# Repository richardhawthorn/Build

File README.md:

### Description

'Build' is an interchangeable set of input/output boards that let you create a complex system of sensors, buttons, actuators, transmitters and screens. Build starts with a wifi base and adds 13 different individually addressed i/o boards.  All boards clip together using a standard 6 pin header, so expanding the system quick and easy. 

This work is licensed under a Creative Commons Attribution-ShareAlike 4.0 International License.

<br />
Designed by <a xmlns:cc="http://creativecommons.org/ns#" href="http://www.richardhawthorn.com" property="cc:attributionName" rel="cc:attributionURL" target="_blank">Richard Hawthorn</a><br />
<a rel="license" href="http://creativecommons.org/licenses/by-sa/4.0/" target="_blank">View License</a>

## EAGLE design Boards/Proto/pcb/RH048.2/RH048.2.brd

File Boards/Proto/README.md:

### Description

Prototype board for use in build system

### Features

- Prototype space
- 3.3v operation

### License

This work is licensed under a Creative Commons Attribution-ShareAlike 4.0 International License.

<br />
Designed by <a xmlns:cc="http://creativecommons.org/ns#" href="http://www.richardhawthorn.com" property="cc:attributionName" rel="cc:attributionURL" target="_blank">Richard Hawthorn</a><br />
<a rel="license" href="http://creativecommons.org/licenses/by-sa/4.0/" target="_blank">View License</a>

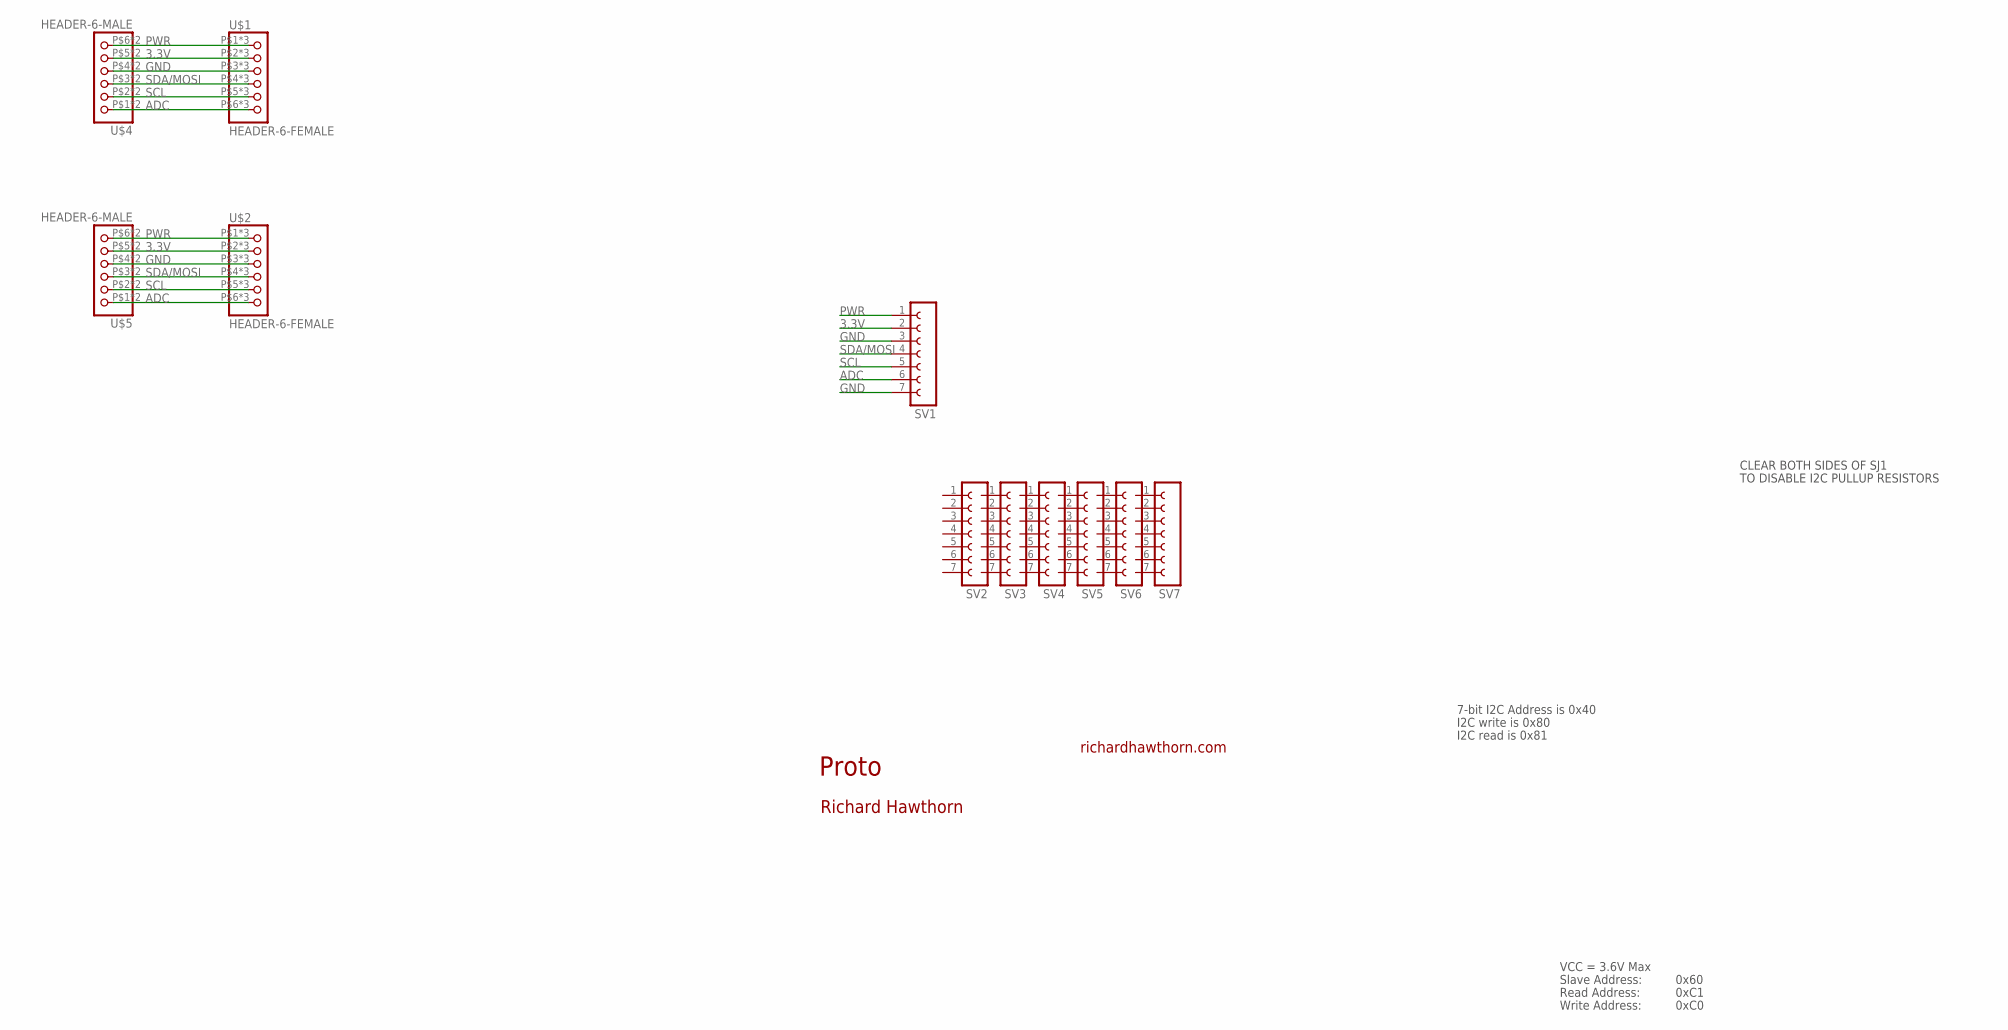
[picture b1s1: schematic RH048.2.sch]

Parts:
SV1, SV2, SV3, SV4, SV5, SV6, SV7: FE07-1; FE07
U$1, U$2: HEADER-6-FEMALE; 2MMHEADER6
U$4, U$5: HEADER-6-MALE; 2MMHEADERPIN6

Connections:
3.3V: SV1.2, U$1.P$2 (2), U$1.P$10 (2), U$1.P$18 (2), U$2.P$2 (2), U$2.P$10 (2), U$2.P$18 (2), U$4.P$5 (5), U$4.P$13 (5), U$5.P$5 (5), U$5.P$13 (5)
ADC: SV1.6, U$1.P$6 (6), U$1.P$14 (6), U$1.P$22 (6), U$2.P$6 (6), U$2.P$14 (6), U$2.P$22 (6), U$4.P$1 (1), U$4.P$9 (1), U$5.P$1 (1), U$5.P$9 (1)
GND: SV1.3, SV1.7, U$1.P$3 (3), U$1.P$11 (3), U$1.P$19 (3), U$2.P$3 (3), U$2.P$11 (3), U$2.P$19 (3), U$4.P$4 (4), U$4.P$12 (4), U$5.P$4 (4), U$5.P$12 (4)
PWR: SV1.1, U$1.P$1 (1), U$1.P$9 (1), U$1.P$17 (1), U$2.P$1 (1), U$2.P$9 (1), U$2.P$17 (1), U$4.P$6 (6), U$4.P$14 (6), U$5.P$6 (6), U$5.P$14 (6)
SCL: SV1.5, U$1.P$5 (5), U$1.P$13 (5), U$1.P$21 (5), U$2.P$5 (5), U$2.P$13 (5), U$2.P$21 (5), U$4.P$2 (2), U$4.P$10 (2), U$5.P$2 (2), U$5.P$10 (2)
SDA/MOSI: SV1.4, U$1.P$4 (4), U$1.P$12 (4), U$1.P$20 (4), U$2.P$4 (4), U$2.P$12 (4), U$2.P$20 (4), U$4.P$3 (3), U$4.P$11 (3), U$5.P$3 (3), U$5.P$11 (3)

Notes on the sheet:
Proto
richardhawthorn.com
Richard Hawthorn
CLEAR BOTH SIDES OF SJ1
TO DISABLE I2C PULLUP RESISTORS
7-bit I2C Address is 0x40
I2C write is 0x80
I2C read is 0x81
VCC = 3.6V Max
Read Address:
Write Address:
Slave Address:
0x60
0xC1
0xC0

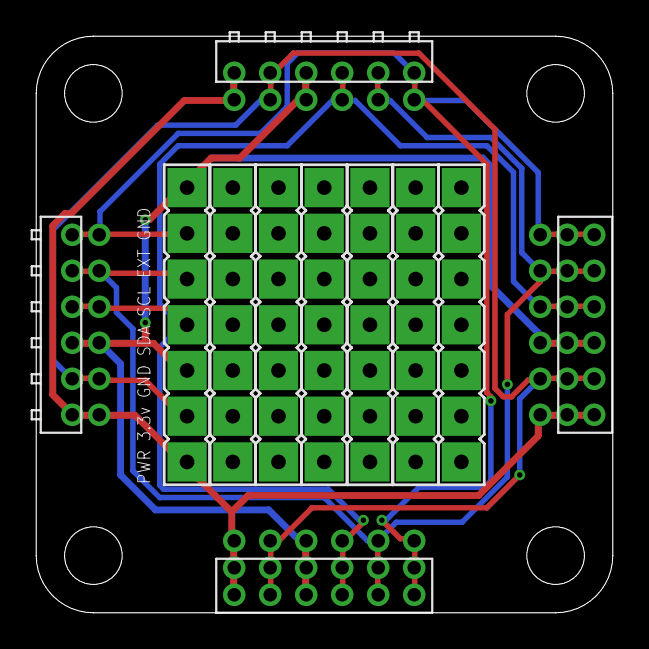
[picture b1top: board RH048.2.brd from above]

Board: 2 copper layers, 32.0 x 32.0 mm, 12 parts (1 on the bottom side), 6 nets.

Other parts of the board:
U$3: OSHW-LOGO-S

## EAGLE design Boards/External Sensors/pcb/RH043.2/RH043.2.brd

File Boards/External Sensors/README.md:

### Description

External sensor board for use in build system

### Features

- 4 x input terminals
- Jack connector for power monitoring (using CT013-100A)
- ATtiny44 processor
- DIL switch for 8 board addresses
- i2c communication with base
- 3.3v operation
- Surface mount

### License

This work is licensed under a Creative Commons Attribution-ShareAlike 4.0 International License.

<br />
Designed by <a xmlns:cc="http://creativecommons.org/ns#" href="http://www.richardhawthorn.com" property="cc:attributionName" rel="cc:attributionURL" target="_blank">Richard Hawthorn</a><br />
<a rel="license" href="http://creativecommons.org/licenses/by-sa/4.0/" target="_blank">View License</a>

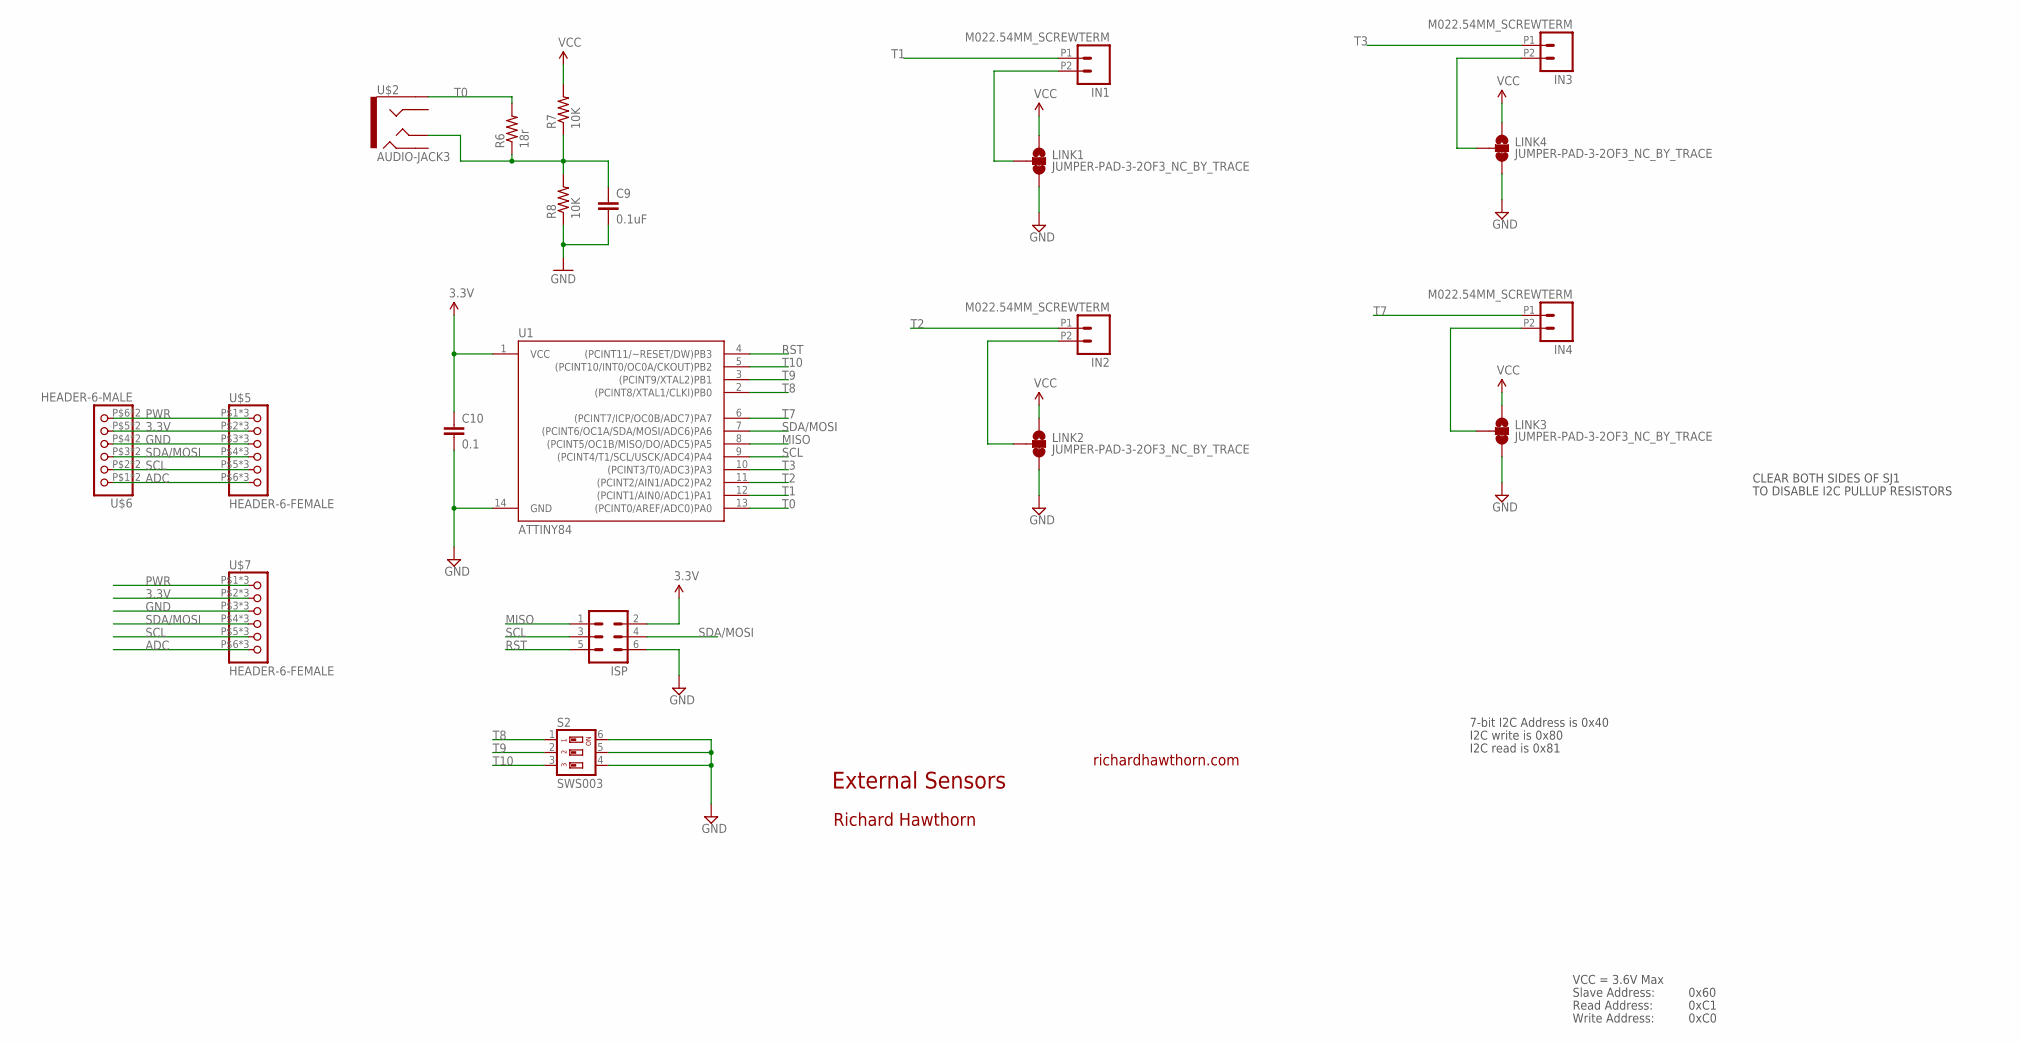
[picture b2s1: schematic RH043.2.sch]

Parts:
C9: 0.1uF; 0603-CAP
C10: 0.1; 0603-CAP
IN1, IN2, IN3, IN4: M022.54MM_SCREWTERM; 1X02_2.54_SCREWTERM
ISP: MA03-2
LINK1, LINK2, LINK3, LINK4: JUMPER-PAD-3-2OF3_NC_BY_TRACE; PAD-JUMPER-3-2OF3_NC_BY_TRACE_YES_SILK_FULL_BOX
R6: 18r; 0603-RES
R7, R8: 10K; 0603-RES
S2: SWS003; SMS-003
U1: ATTINY84; SO14
U$2: AUDIO-JACK3; AUDIO-JACK-TRRS-SMD
U$5, U$7: HEADER-6-FEMALE; 2MMHEADER6
U$6: HEADER-6-MALE; 2MMHEADERPIN6

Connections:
3.3V: C10.1, ISP.2, LINK1.1, LINK2.1, LINK3.1, LINK4.1, R7.2, U1.1 (VCC), U$5.P$2 (2), U$5.P$10 (2), U$5.P$18 (2), U$6.P$5 (5), U$6.P$13 (5), U$7.P$2 (2), U$7.P$10 (2), U$7.P$18 (2)
ADC: U$5.P$6 (6), U$5.P$14 (6), U$5.P$22 (6), U$6.P$1 (1), U$6.P$9 (1), U$7.P$6 (6), U$7.P$14 (6), U$7.P$22 (6)
GND: C9.2, C10.2, ISP.6, LINK1.3, LINK2.3, LINK3.3, LINK4.3, R8.1, S2.4, S2.5, S2.6, U1.14 (GND), U$5.P$3 (3), U$5.P$11 (3), U$5.P$19 (3), U$6.P$4 (4), U$6.P$12 (4), U$7.P$3 (3), U$7.P$11 (3), U$7.P$19 (3)
MISO: ISP.1, U1.8 ((PCINT5/OC1B/MISO/DO/ADC5)PA5)
unnamed: IN3.P2 (2), LINK4.2
unnamed: IN4.P2 (2), LINK3.2
unnamed: IN1.P2 (2), LINK1.2
unnamed: IN2.P2 (2), LINK2.2
PWR: U$5.P$1 (1), U$5.P$9 (1), U$5.P$17 (1), U$6.P$6 (6), U$6.P$14 (6), U$7.P$1 (1), U$7.P$9 (1), U$7.P$17 (1)
R6: C9.1, R6.1, R7.1, R8.2, U$2.TIP
RST: ISP.5, U1.4 ((PCINT11/~RESET/DW)PB3)
SCL: ISP.3, U1.9 ((PCINT4/T1/SCL/USCK/ADC4)PA4), U$5.P$5 (5), U$5.P$13 (5), U$5.P$21 (5), U$6.P$2 (2), U$6.P$10 (2), U$7.P$5 (5), U$7.P$13 (5), U$7.P$21 (5)
SDA/MOSI: ISP.4, U1.7 ((PCINT6/OC1A/SDA/MOSI/ADC6)PA6), U$5.P$4 (4), U$5.P$12 (4), U$5.P$20 (4), U$6.P$3 (3), U$6.P$11 (3), U$7.P$4 (4), U$7.P$12 (4), U$7.P$20 (4)
T0: R6.2, U1.13 ((PCINT0/AREF/ADC0)PA0), U$2.EARTH
T1: IN1.P1 (1), U1.12 ((PCINT1/AIN0/ADC1)PA1)
T2: IN2.P1 (1), U1.11 ((PCINT2/AIN1/ADC2)PA2)
T3: IN3.P1 (1), U1.10 ((PCINT3/T0/ADC3)PA3)
T7: IN4.P1 (1), U1.6 ((PCINT7/ICP/OC0B/ADC7)PA7)
T8: S2.1, U1.2 ((PCINT8/XTAL1/CLKI)PB0)
T9: S2.2, U1.3 ((PCINT9/XTAL2)PB1)
T10: S2.3, U1.5 ((PCINT10/INT0/OC0A/CKOUT)PB2)

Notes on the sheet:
External Sensors
richardhawthorn.com
Richard Hawthorn
CLEAR BOTH SIDES OF SJ1
TO DISABLE I2C PULLUP RESISTORS
7-bit I2C Address is 0x40
I2C write is 0x80
I2C read is 0x81
VCC = 3.6V Max
Read Address:
Write Address:
Slave Address:
0x60
0xC1
0xC0

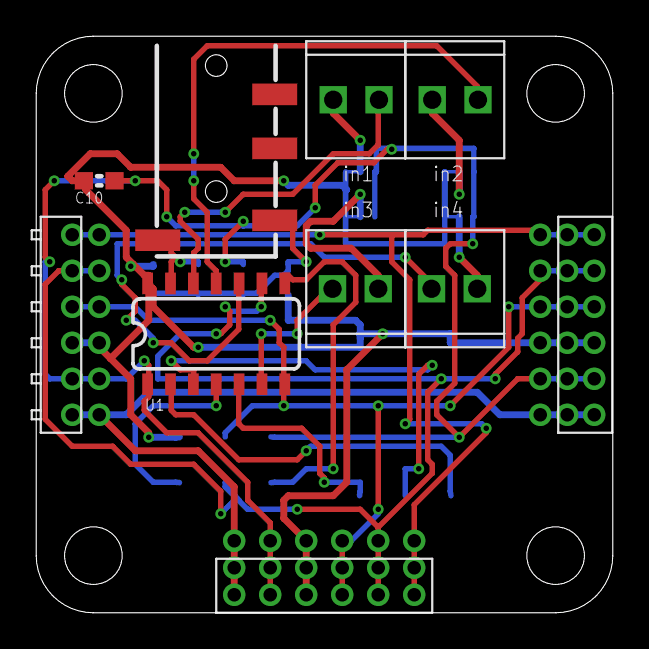
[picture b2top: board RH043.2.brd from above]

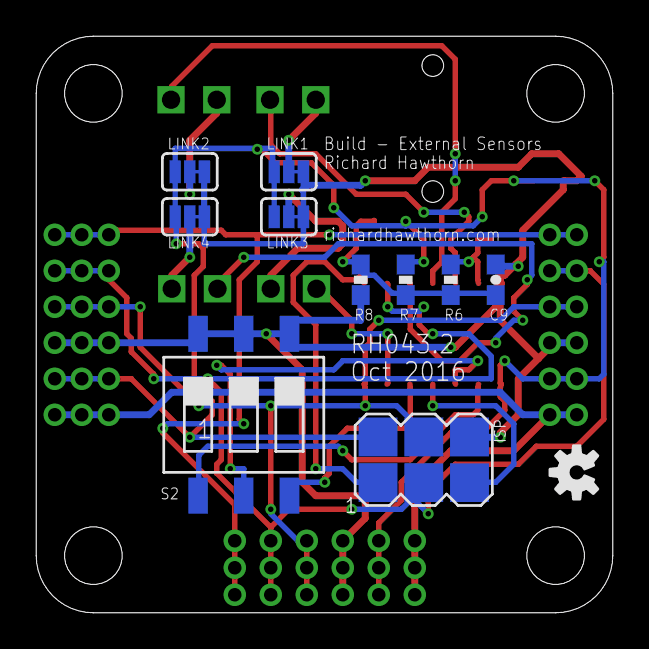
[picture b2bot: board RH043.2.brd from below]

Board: 2 copper layers, 32.0 x 32.0 mm, 21 parts (11 on the bottom side), 21 nets.

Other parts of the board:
U$3: OSHW-LOGO-S

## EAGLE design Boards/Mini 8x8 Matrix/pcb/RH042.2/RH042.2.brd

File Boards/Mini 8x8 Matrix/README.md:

### Description

Mini 8x8 LED matrix board for use in build system

### Features

- 8x8 matrix LED screen
- HT16K33 LED driver
- DIL switch for 2 board addresses
- i2c communication with base
- 3.3v operation
- Surface mount

### License

This work is licensed under a Creative Commons Attribution-ShareAlike 4.0 International License.

<br />
Designed by <a xmlns:cc="http://creativecommons.org/ns#" href="http://www.richardhawthorn.com" property="cc:attributionName" rel="cc:attributionURL" target="_blank">Richard Hawthorn</a><br />
<a rel="license" href="http://creativecommons.org/licenses/by-sa/4.0/" target="_blank">View License</a>

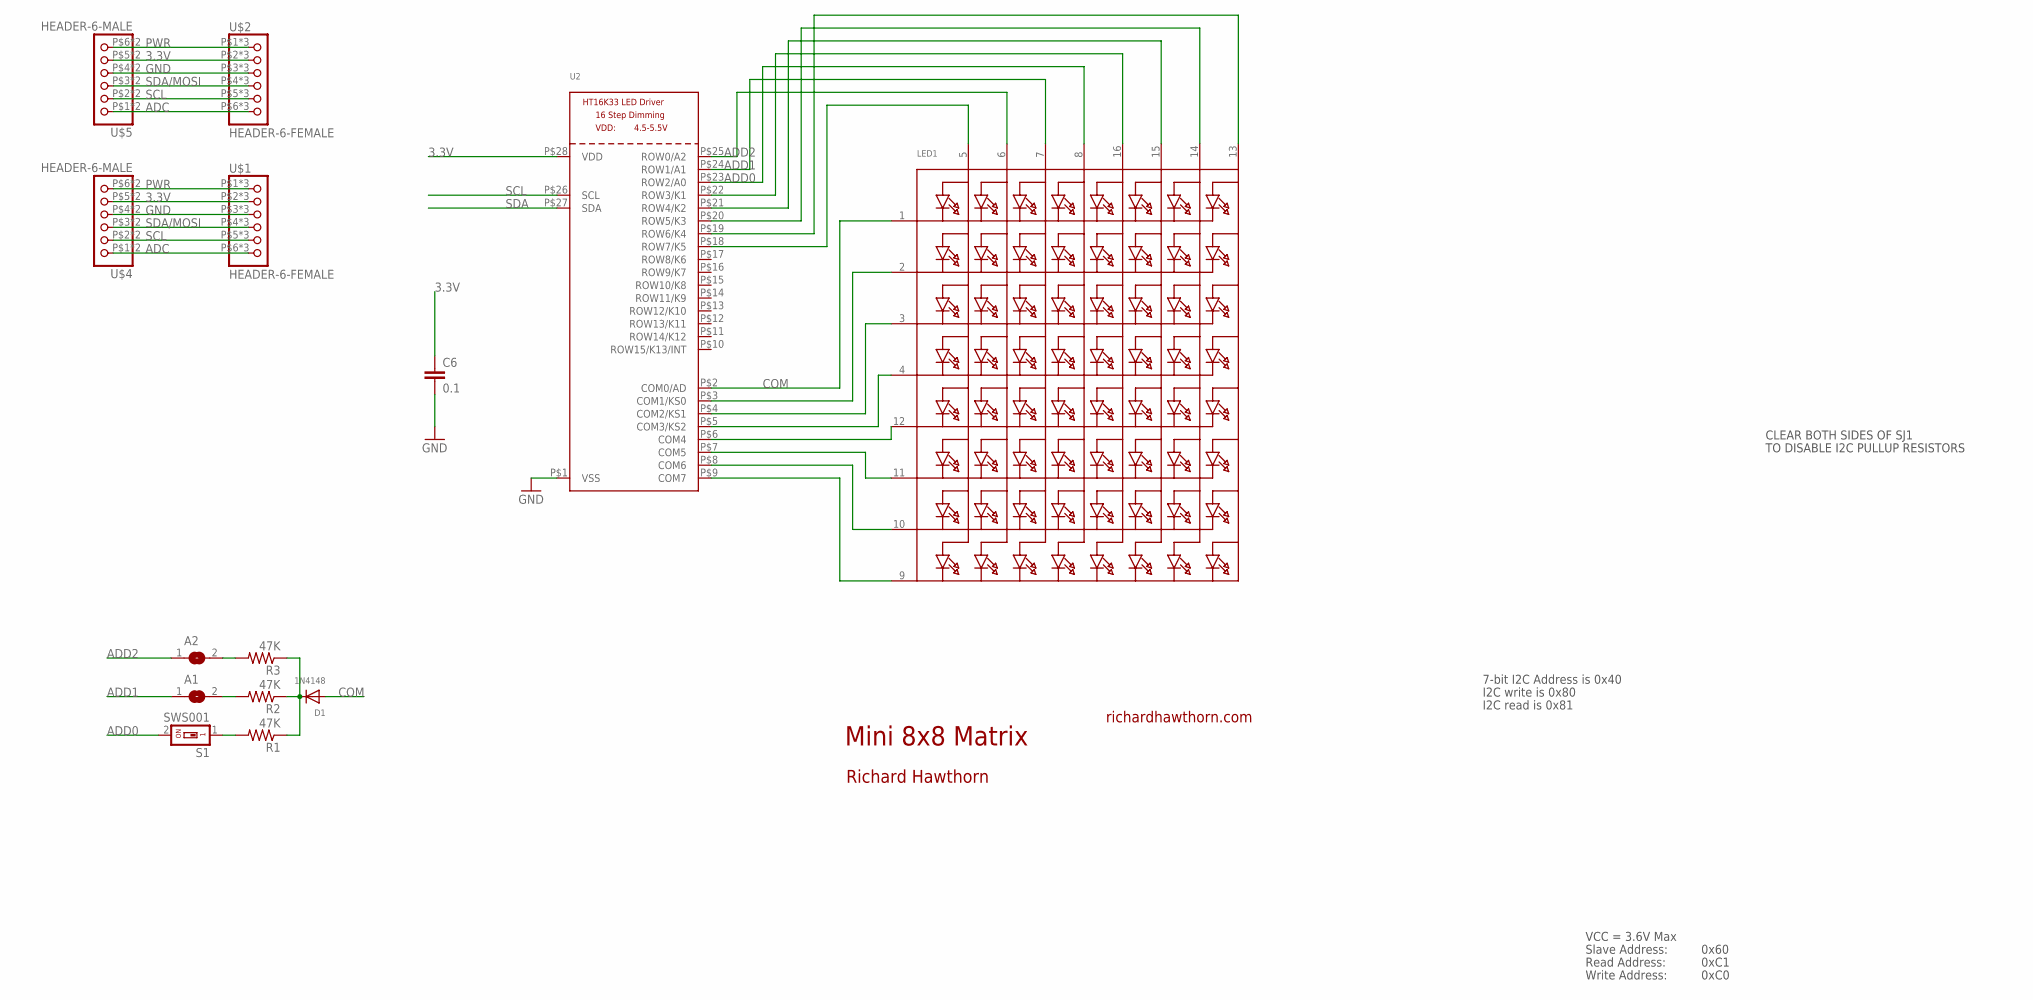
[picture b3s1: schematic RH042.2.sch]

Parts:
A1, A2: SJ
C6: 0.1; 0603-CAP
D1: 1N4148; SOD-323F
LED1: SEGMENT_8X8_ROWCATHODE; SEGMENT_BL-M07C881UR
R1, R2, R3: 47K; R0805
S1: SWS001; SMS-001
U2: HT16K33_SOP28; SOP28_300MIL
U$1, U$2: HEADER-6-FEMALE; 2MMHEADER6
U$4, U$5: HEADER-6-MALE; 2MMHEADERPIN6

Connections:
3.3V: C6.1, U2.P$28 (VDD), U$1.P$2 (2), U$1.P$10 (2), U$1.P$18 (2), U$2.P$2 (2), U$2.P$10 (2), U$2.P$18 (2), U$4.P$5 (5), U$4.P$13 (5), U$5.P$5 (5), U$5.P$13 (5)
ADC: U$1.P$6 (6), U$1.P$14 (6), U$1.P$22 (6), U$2.P$6 (6), U$2.P$14 (6), U$2.P$22 (6), U$4.P$1 (1), U$4.P$9 (1), U$5.P$1 (1), U$5.P$9 (1)
ADD0: LED1.8 (A4), S1.2, U2.P$23 (ROW2/A0)
ADD1: A1.1, LED1.7 (A3), U2.P$24 (ROW1/A1)
ADD2: A2.1, LED1.6 (A2), U2.P$25 (ROW0/A2)
COM: D1.A, LED1.1 (K1), U2.P$2 (COM0/AD)
GND: C6.2, U2.P$1 (VSS), U$1.P$3 (3), U$1.P$11 (3), U$1.P$19 (3), U$2.P$3 (3), U$2.P$11 (3), U$2.P$19 (3), U$4.P$4 (4), U$4.P$12 (4), U$5.P$4 (4), U$5.P$12 (4)
unnamed: LED1.9 (K8), U2.P$9 (COM7)
unnamed: A2.2, R3.2
unnamed: LED1.10 (K7), U2.P$8 (COM6)
unnamed: LED1.11 (K6), U2.P$7 (COM5)
unnamed: D1.C, R1.1, R2.1, R3.1
unnamed: R1.2, S1.1
unnamed: A1.2, R2.2
unnamed: LED1.12 (K5), U2.P$6 (COM4)
unnamed: LED1.4 (K4), U2.P$5 (COM3/KS2)
unnamed: LED1.3 (K3), U2.P$4 (COM2/KS1)
unnamed: LED1.2 (K2), U2.P$3 (COM1/KS0)
unnamed: LED1.16 (A5), U2.P$22 (ROW3/K1)
unnamed: LED1.15 (A6), U2.P$21 (ROW4/K2)
unnamed: LED1.5 (A1), U2.P$18 (ROW7/K5)
PWR: U$1.P$1 (1), U$1.P$9 (1), U$1.P$17 (1), U$2.P$1 (1), U$2.P$9 (1), U$2.P$17 (1), U$4.P$6 (6), U$4.P$14 (6), U$5.P$6 (6), U$5.P$14 (6)
SCL: U2.P$26 (SCL), U$1.P$5 (5), U$1.P$13 (5), U$1.P$21 (5), U$2.P$5 (5), U$2.P$13 (5), U$2.P$21 (5), U$4.P$2 (2), U$4.P$10 (2), U$5.P$2 (2), U$5.P$10 (2)
SDA: U2.P$27 (SDA)
SDA/MOSI: U$1.P$4 (4), U$1.P$12 (4), U$1.P$20 (4), U$2.P$4 (4), U$2.P$12 (4), U$2.P$20 (4), U$4.P$3 (3), U$4.P$11 (3), U$5.P$3 (3), U$5.P$11 (3)
SEG_F: LED1.14 (A7), U2.P$20 (ROW5/K3)
SEG_G: LED1.13 (A8), U2.P$19 (ROW6/K4)

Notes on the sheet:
Mini 8x8 Matrix
richardhawthorn.com
Richard Hawthorn
CLEAR BOTH SIDES OF SJ1
TO DISABLE I2C PULLUP RESISTORS
7-bit I2C Address is 0x40
I2C write is 0x80
I2C read is 0x81
VCC = 3.6V Max
Read Address:
Write Address:
Slave Address:
0x60
0xC1
0xC0

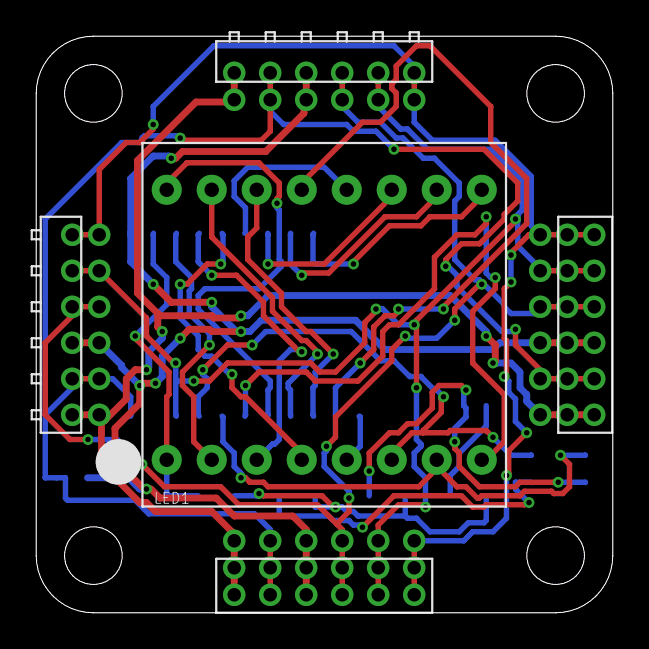
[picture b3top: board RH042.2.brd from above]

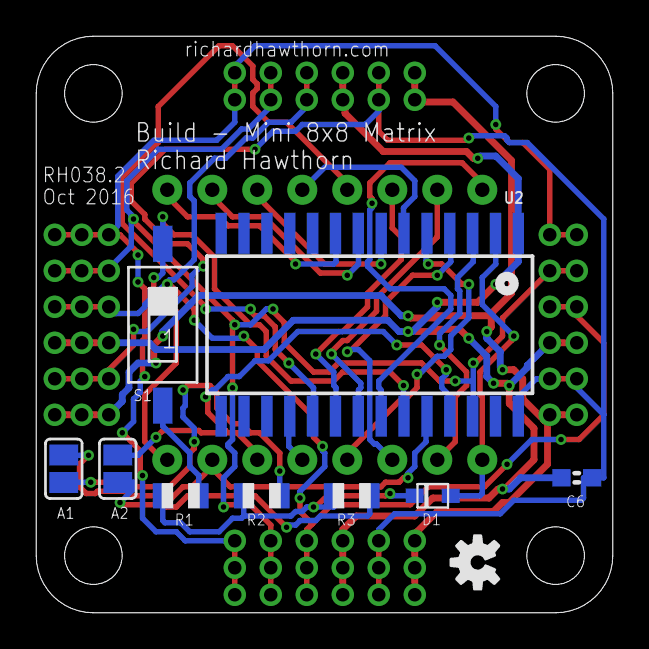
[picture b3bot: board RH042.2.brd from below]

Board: 2 copper layers, 32.0 x 32.0 mm, 15 parts (10 on the bottom side), 26 nets.

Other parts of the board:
U$3: OSHW-LOGO-S

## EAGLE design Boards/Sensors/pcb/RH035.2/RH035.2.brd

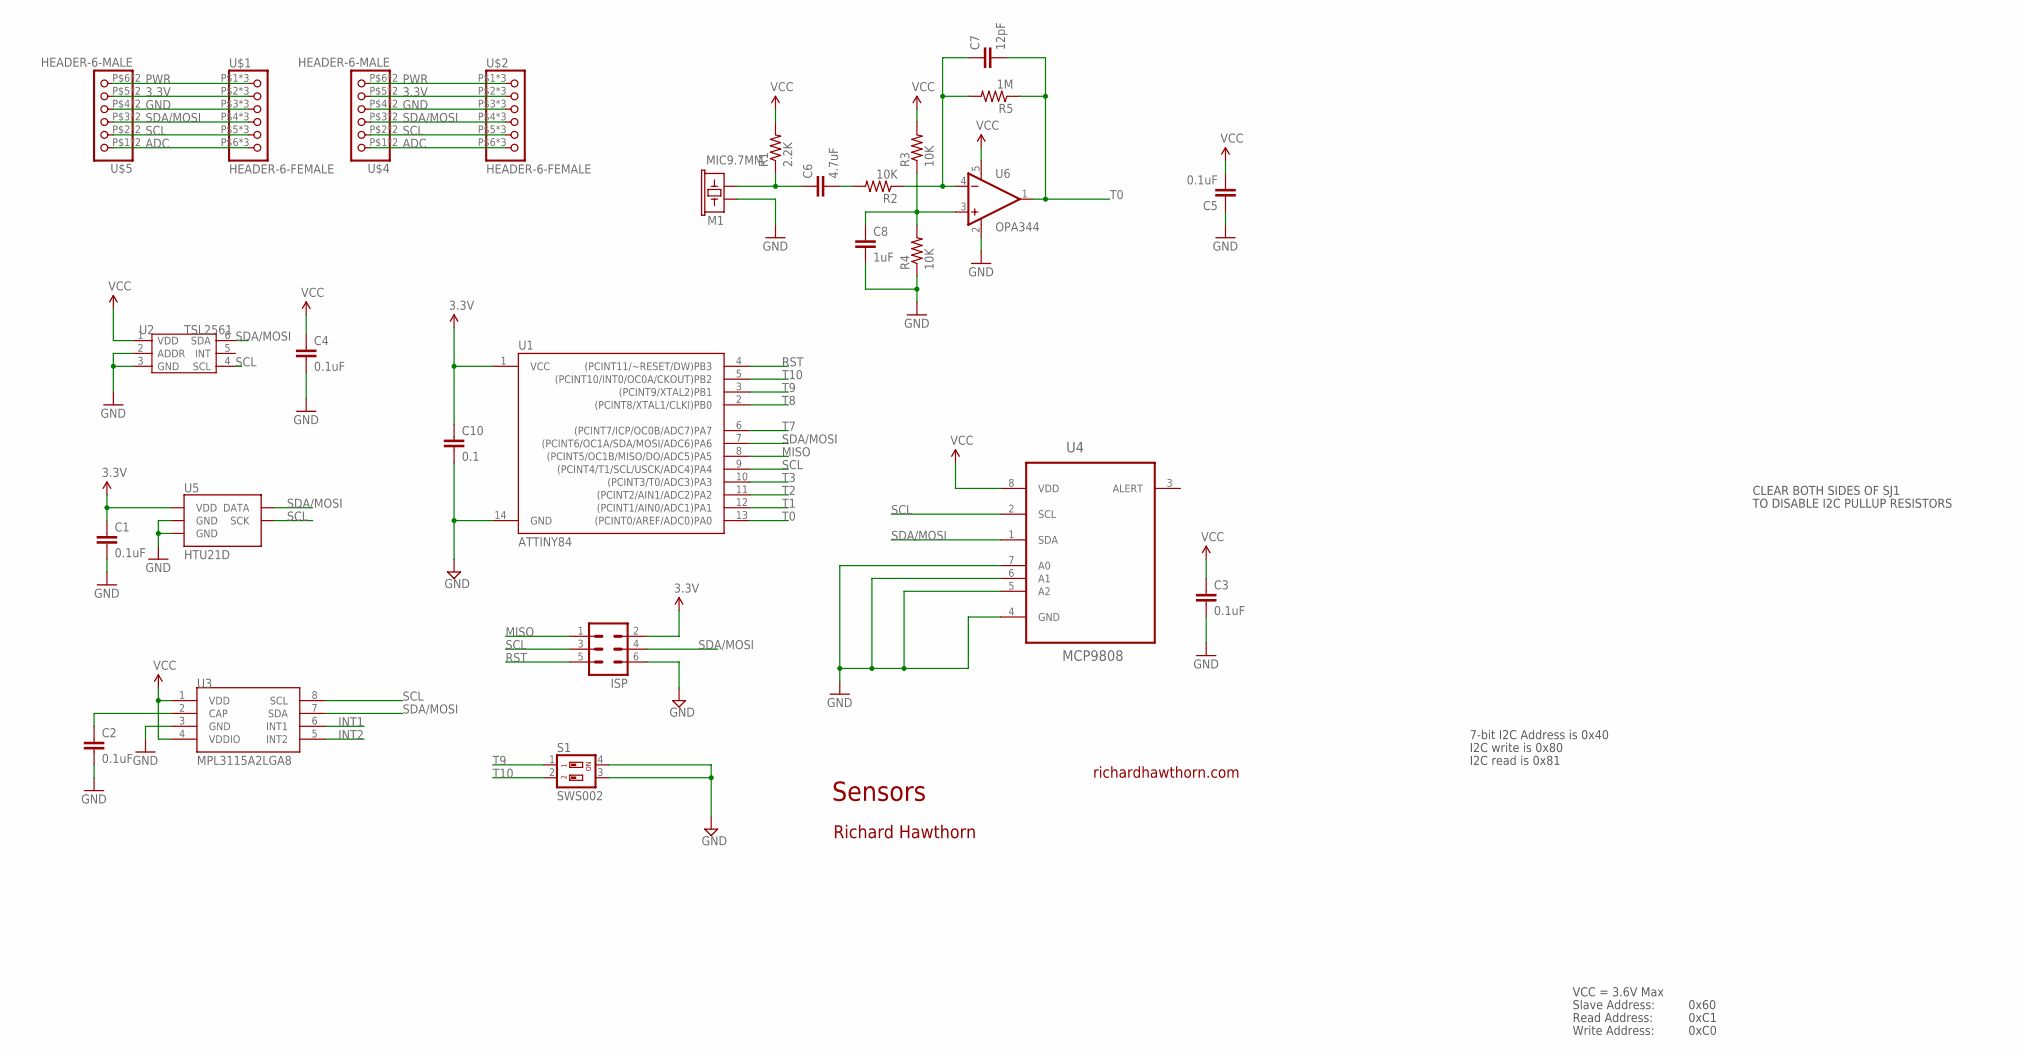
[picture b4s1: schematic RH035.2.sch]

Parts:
C1, C2, C5: 0.1uF; 0805
C3, C4: 0.1uF; 0603-CAP
C6: 4.7uF; 0805
C7: 12pF; 0805
C8: 1uF; 0805
C10: 0.1; 0603-CAP
ISP: MA03-2
M1: MIC9.7MM; MIC-9.7MM
R1: 2.2K; 0805
R2, R3, R4: 10K; 0805
R5: 1M; 0805
S1: SWS002; SMS-002
U1: ATTINY84; SO14
U2: TSL2561; TMB-6
U3: MPL3115A2LGA8; LGA8
U4: MCP9808; SOP65P490X110-8N
U5: HTU21D
U6: OPA344; SOT23-5
U$1, U$2: HEADER-6-FEMALE; 2MMHEADER6
U$4, U$5: HEADER-6-MALE; 2MMHEADERPIN6

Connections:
3.3V: C1.1, C3.1, C4.1, C5.2, C10.1, ISP.2, R1.2, R3.2, U1.1 (VCC), U2.1 (VDD), U3.1 (VDD), U3.4 (VDDIO), U4.8 (VDD), U5.VDD, U6.5 (V+), U$1.P$2 (2), U$1.P$10 (2), U$1.P$18 (2), U$2.P$2 (2), U$2.P$10 (2), U$2.P$18 (2), U$4.P$5 (5), U$4.P$13 (5), U$5.P$5 (5), U$5.P$13 (5)
ADC: U$1.P$6 (6), U$1.P$14 (6), U$1.P$22 (6), U$2.P$6 (6), U$2.P$14 (6), U$2.P$22 (6), U$4.P$1 (1), U$4.P$9 (1), U$5.P$1 (1), U$5.P$9 (1)
GND: C1.2, C2.2, C3.2, C4.2, C5.1, C8.2, C10.2, ISP.6, M1.2, R4.1, S1.3, S1.4, U1.14 (GND), U2.2 (ADDR), U2.3 (GND), U3.3 (GND), U4.4 (GND), U4.5 (A2), U4.6 (A1), U4.7 (A0), U5.7 (GND), U5.GND, U6.2 (V-), U$1.P$3 (3), U$1.P$11 (3), U$1.P$19 (3), U$2.P$3 (3), U$2.P$11 (3), U$2.P$19 (3), U$4.P$4 (4), U$4.P$12 (4), U$5.P$4 (4), U$5.P$12 (4)
INT1: U3.6 (INT1)
INT2: U3.5 (INT2)
MISO: ISP.1, U1.8 ((PCINT5/OC1B/MISO/DO/ADC5)PA5)
unnamed: C6.1, M1.1, R1.1
unnamed: C7.1, R2.1, R5.2, U6.4 (-IN)
unnamed: C6.2, R2.2
unnamed: C8.1, R3.1, R4.2, U6.3 (+IN)
unnamed: C2.1, U3.2 (CAP)
PWR: U$1.P$1 (1), U$1.P$9 (1), U$1.P$17 (1), U$2.P$1 (1), U$2.P$9 (1), U$2.P$17 (1), U$4.P$6 (6), U$4.P$14 (6), U$5.P$6 (6), U$5.P$14 (6)
RST: ISP.5, U1.4 ((PCINT11/~RESET/DW)PB3)
SCL: ISP.3, U1.9 ((PCINT4/T1/SCL/USCK/ADC4)PA4), U2.4 (SCL), U3.8 (SCL), U4.2 (SCL), U5.SCK, U$1.P$5 (5), U$1.P$13 (5), U$1.P$21 (5), U$2.P$5 (5), U$2.P$13 (5), U$2.P$21 (5), U$4.P$2 (2), U$4.P$10 (2), U$5.P$2 (2), U$5.P$10 (2)
SDA/MOSI: ISP.4, U1.7 ((PCINT6/OC1A/SDA/MOSI/ADC6)PA6), U2.6 (SDA), U3.7 (SDA), U4.1 (SDA), U5.DATA, U$1.P$4 (4), U$1.P$12 (4), U$1.P$20 (4), U$2.P$4 (4), U$2.P$12 (4), U$2.P$20 (4), U$4.P$3 (3), U$4.P$11 (3), U$5.P$3 (3), U$5.P$11 (3)
T0: C7.2, R5.1, U1.13 ((PCINT0/AREF/ADC0)PA0), U6.1 (OUT)
T1: U1.12 ((PCINT1/AIN0/ADC1)PA1)
T2: U1.11 ((PCINT2/AIN1/ADC2)PA2)
T3: U1.10 ((PCINT3/T0/ADC3)PA3)
T7: U1.6 ((PCINT7/ICP/OC0B/ADC7)PA7)
T8: U1.2 ((PCINT8/XTAL1/CLKI)PB0)
T9: S1.1, U1.3 ((PCINT9/XTAL2)PB1)
T10: S1.2, U1.5 ((PCINT10/INT0/OC0A/CKOUT)PB2)

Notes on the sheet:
Sensors
richardhawthorn.com
Richard Hawthorn
CLEAR BOTH SIDES OF SJ1
TO DISABLE I2C PULLUP RESISTORS
7-bit I2C Address is 0x40
I2C write is 0x80
I2C read is 0x81
VCC = 3.6V Max
Read Address:
Write Address:
Slave Address:
0x60
0xC1
0xC0

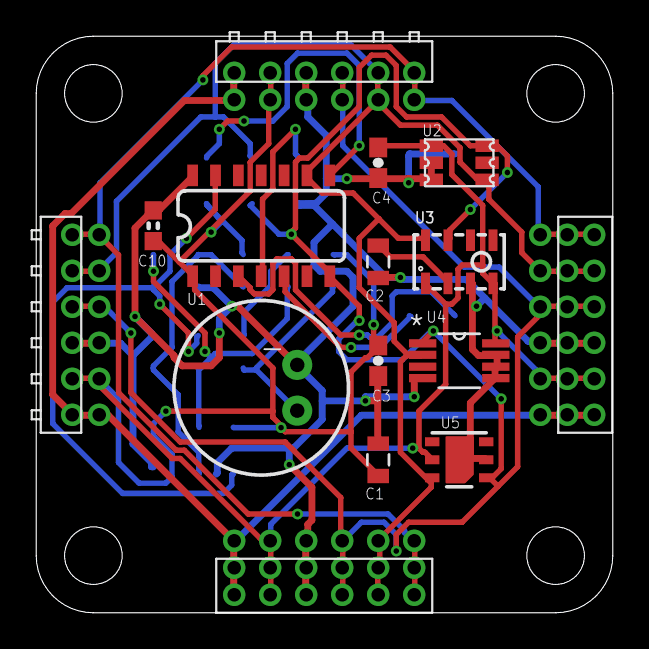
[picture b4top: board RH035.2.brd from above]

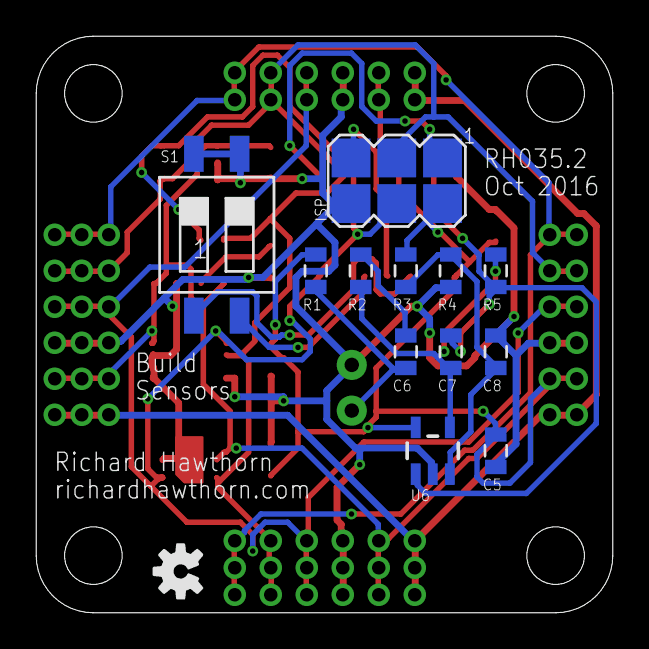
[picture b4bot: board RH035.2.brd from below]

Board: 2 copper layers, 32.0 x 32.0 mm, 28 parts (13 on the bottom side), 16 nets.

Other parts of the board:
U$3: OSHW-LOGO-S

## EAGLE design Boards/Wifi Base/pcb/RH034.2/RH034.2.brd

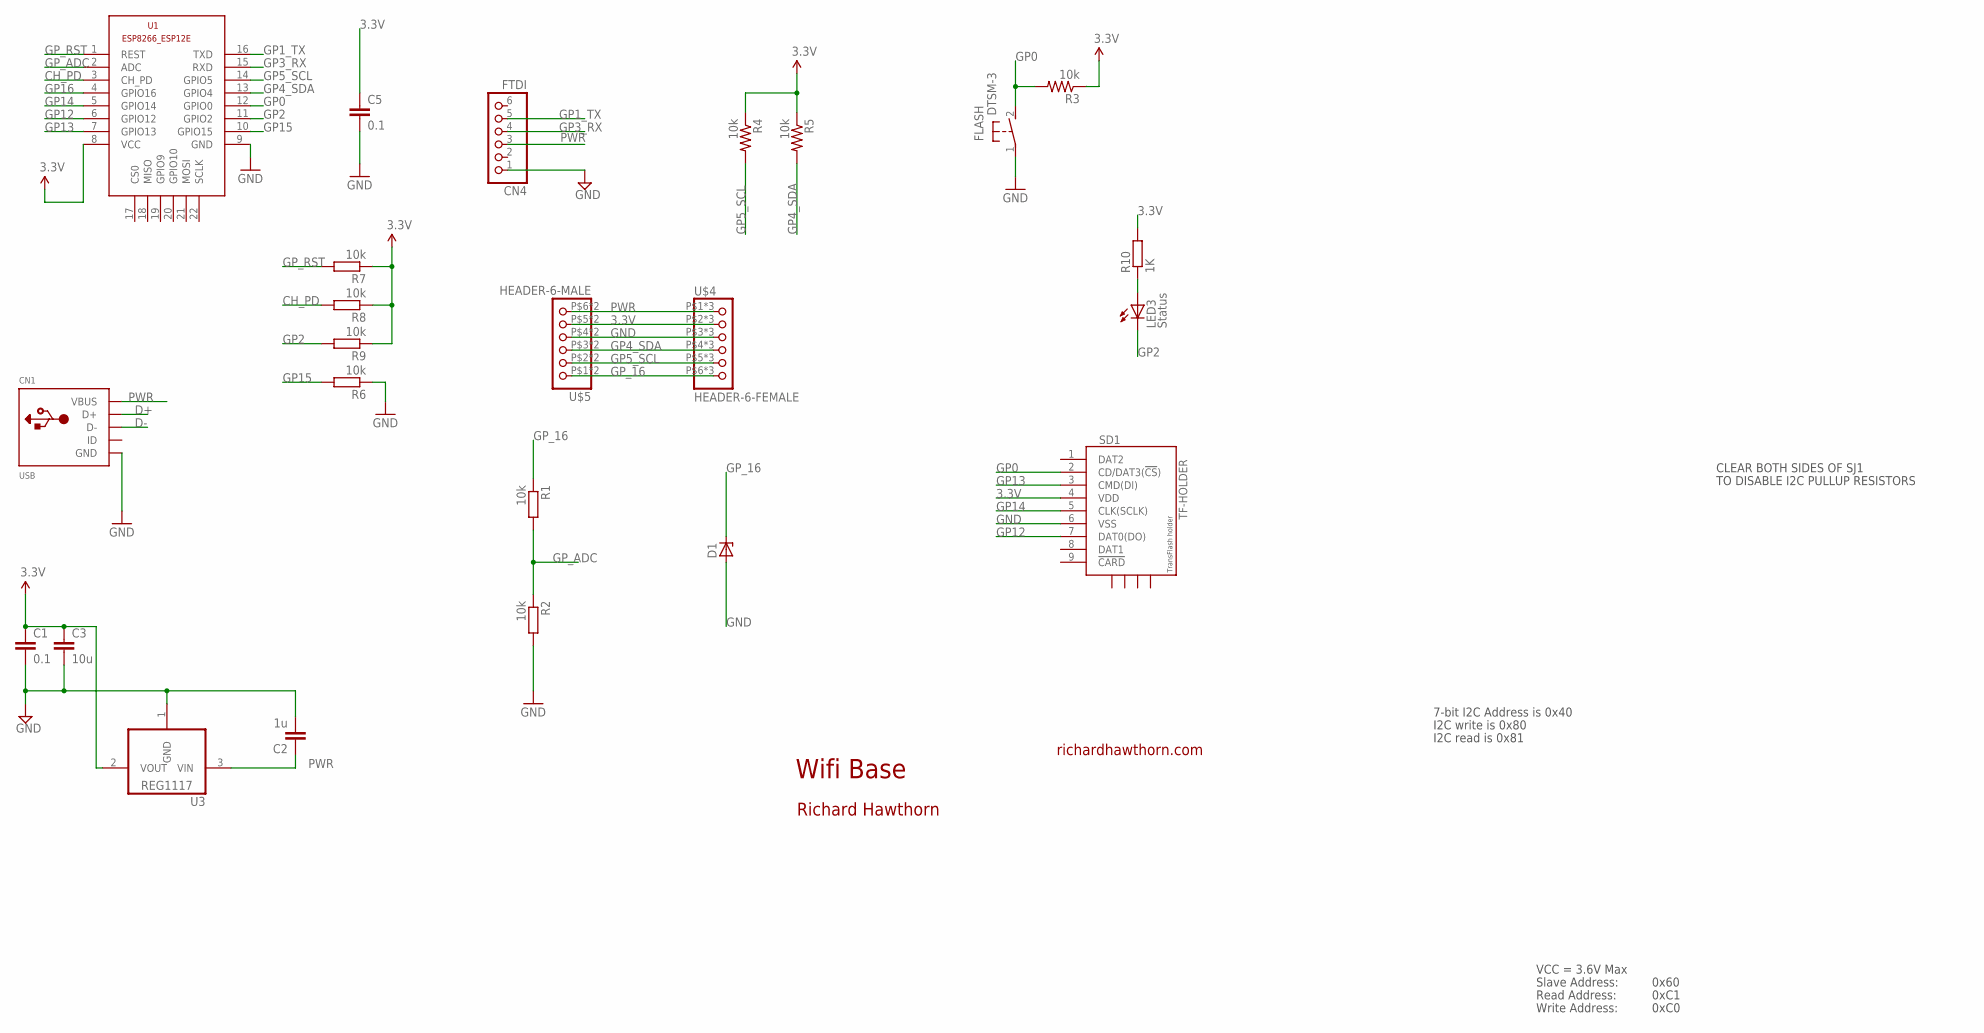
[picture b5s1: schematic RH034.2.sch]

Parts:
C1, C5: 0.1; 0603-CAP
C2: 1u; 0603-CAP
C3: 10u; 0805-CAP
CN1: USB; USB-MINIB
CN4: FTDI; 1X06
D1: ZENER-DIODESOT23; SOT23
FLASH: DTSM-3
LED3: Status; CHIPLED_0805
R1, R2, R6, R7, R8, R9: 10k; R0603
R3, R4, R5: 10k; 0805
R10: 1K; R0603
SD1: TF-HOLDER; TF-PULL
U1: ESP8266-12EESP8266-ESP12E; ESP8266-ESP12E
U3: REG1117; SOT223
U$4: HEADER-6-FEMALE; 2MMHEADER6
U$5: HEADER-6-MALE; 2MMHEADERPIN6

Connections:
3.3V: C1.1, C3.1, C5.1, R3.1, R4.1, R5.1, R7.1, R8.1, R9.1, R10.2, SD1.4 (VDD), U1.8 (VCC), U3.2 (VOUT), U$4.P$2 (2), U$4.P$10 (2), U$4.P$18 (2), U$5.P$5 (5), U$5.P$13 (5)
CH_PD: R8.2, U1.3 (CH_PD)
D+: CN1.D+
D-: CN1.D-
GND: C1.2, C2.2, C3.2, C5.2, CN1.GND, CN4.1, D1.1 (A), FLASH.1, R2.2, R6.1, SD1.6 (VSS), U1.9 (GND), U3.1 (GND), U$4.P$3 (3), U$4.P$11 (3), U$4.P$19 (3), U$5.P$4 (4), U$5.P$12 (4)
GP0: FLASH.2, R3.2, SD1.2 (CD/DAT3(!CS!)), U1.12 (GPIO0)
GP1_TX: CN4.5, U1.16 (TXD)
GP2: LED3.C, R9.2, U1.11 (GPIO2)
GP3_RX: CN4.4, U1.15 (RXD)
GP4_SDA: R5.2, U1.13 (GPIO4), U$4.P$4 (4), U$4.P$12 (4), U$4.P$20 (4), U$5.P$3 (3), U$5.P$11 (3)
GP5_SCL: R4.2, U1.14 (GPIO5), U$4.P$5 (5), U$4.P$13 (5), U$4.P$21 (5), U$5.P$2 (2), U$5.P$10 (2)
GP12: SD1.7 (DAT0(DO)), U1.6 (GPIO12)
GP13: SD1.3 (CMD(DI)), U1.7 (GPIO13)
GP14: SD1.5 (CLK(SCLK)), U1.5 (GPIO14)
GP15: R6.2, U1.10 (GPIO15)
GP16: U1.4 (GPIO16)
GP_16: D1.3 (C), R1.1, U$4.P$6 (6), U$4.P$14 (6), U$4.P$22 (6), U$5.P$1 (1), U$5.P$9 (1)
GP_ADC: R1.2, R2.1, U1.2 (ADC)
GP_RST: R7.2, U1.1 (REST)
unnamed: LED3.A, R10.1
PWR: C2.1, CN1.VBUS, CN4.3, U3.3 (VIN), U$4.P$1 (1), U$4.P$9 (1), U$4.P$17 (1), U$5.P$6 (6), U$5.P$14 (6)

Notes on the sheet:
Wifi Base
richardhawthorn.com
Richard Hawthorn
CLEAR BOTH SIDES OF SJ1
TO DISABLE I2C PULLUP RESISTORS
7-bit I2C Address is 0x40
I2C write is 0x80
I2C read is 0x81
VCC = 3.6V Max
Read Address:
Write Address:
Slave Address:
0x60
0xC1
0xC0

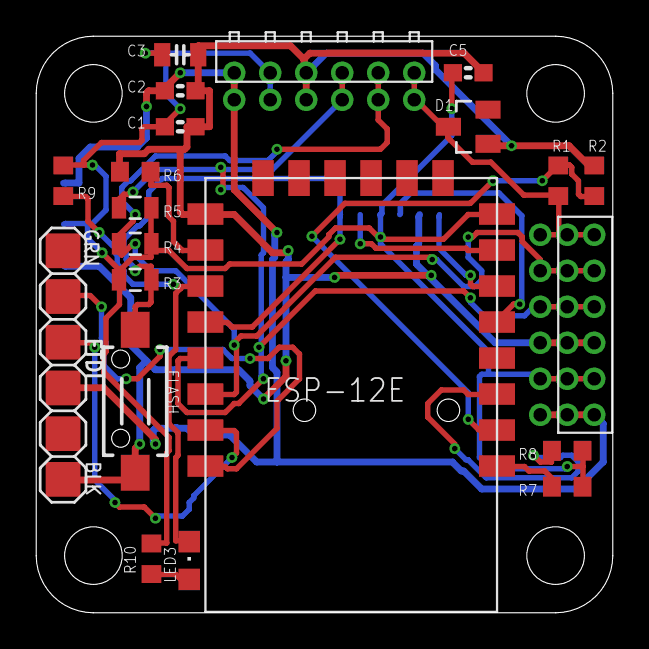
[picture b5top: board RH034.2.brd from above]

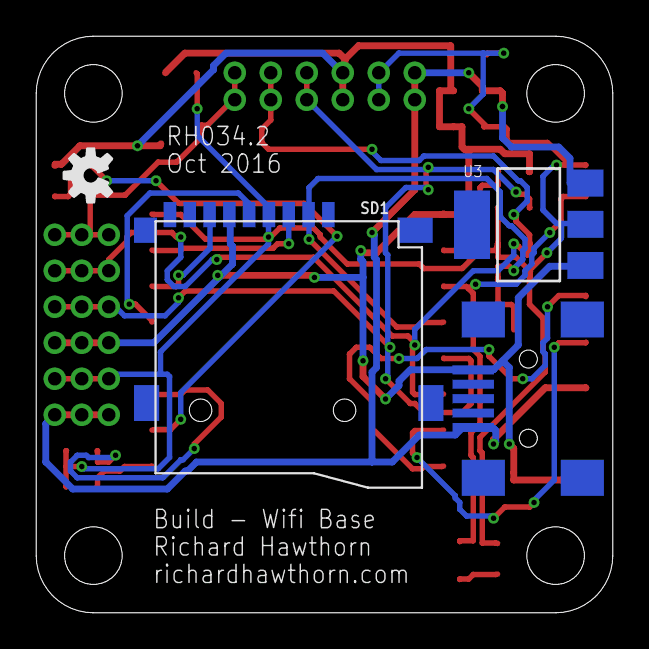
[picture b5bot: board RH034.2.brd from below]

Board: 2 copper layers, 32.0 x 32.0 mm, 25 parts (4 on the bottom side), 18 nets.

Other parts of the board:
U$3: OSHW-LOGO-S

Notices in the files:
README.md:
CC BY-SA 4.0
parts and their libraries:
SparkFun-Aesthetics: Licensing: CC v3.0 Share-Alike You are welcome to use this library for commercial purposes.
SparkFun-DigitalIC: Licensing: Creative Commons ShareAlike 4.0 International - https://creativecommons.org/licenses/by-sa/4.0
